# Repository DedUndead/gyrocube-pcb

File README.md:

# Gyrocube PCB design

Project is ongoing.

## Concept description 

GyroCube is a Smart-Home accessory. The GyroCube is a multipurpose cube that can perform different functions based on the cube placing. The functionality is changed by simply flipping the cube on the table. The functionalities are humidity measurements, OMA notifications, and weather-forecasts. GyroCube uses vibration modules and LEDs as the output method to notify the user of changes.<br><br>
GyroCube consists of the main station and cubes that will be in constant M2M communication. The main station handles the sensor measurements and internet communications, while the cubes react to changes in the main station. Thus, allowing the GyroCube environment to be scalable, as the user can connect as many cubes as he wants. 
The goal is to provide the user with a delightful-looking home accessory, which will also allow them to obtain helpful information in a simple, minimalistic way. 

## Topology example - Star

The HUB acts as Zigbee coordinator/router, while the cubes are end devices of the topology. HUB communicates with Wireless Access Point.

## PCB design description

PCB design for the gyrocube IoT project. Consists of several parts: x6 RGB LED PCBs, cube's MCU and main hub's MCU.
External components were used when designing the schematics

<b>Hub PCB</b>:<br>
[Microcontroller](https://app.ultralibrarian.com/details/23afb9f1-10a0-11e9-ab3a-0a3560a4cccc/Microchip/PIC32MX575F512H-80I-PT?open=backlink)<br>
[RF Tranciever (Zigbee)](https://app.ultralibrarian.com/details/42fe3879-10a0-11e9-ab3a-0a3560a4cccc/Microchip/AT86RF231-ZU?uid=8d6b40c328af52ac)<br>
[Wi-Fi Module](https://app.ultralibrarian.com/details/2b6afdaf-b24e-11ea-b5d0-0aebb021a1ea/Silicon-Labs/WFM200S022XNA2?uid=52bf9d8b68458d78)

<b>Cube MCU</b>:<br>
[Microcontroller](https://app.ultralibrarian.com/details/4b4afbe8-2e28-11eb-9033-0a34d6323d74/Microchip/PIC18F47K40-I-P?uid=9581580b9c884a46&exports=KiCAD&open=exports)<br>
[Gyroscope](https://app.ultralibrarian.com/details/68dbfc0c-1e52-11eb-9033-0a34d6323d74/STMicroelectronics/L3GD20H?uid=c097080110371f50)<br>
Humidity/Temperature sensor is custom. The library is cached in the respective folder.<br>
[Vibration coin](https://www.snapeda.com/parts/C0720B001F/Jinlong%20Machinery%20&amp;%20Electronics,%20Inc./view-part/)

## LED PCB design:

Uses ws2812b-5050 LED and 100-1000 uF filtering capacitor. The exact value is not yet specified.

The LED PCB are connected to each other with wires. The cube's PCB contains the connector to connect the first LED, that starts the series.

## Cube PCB design:

Cube PCB contains the MCU and all the peripherals.

### Cube MCU: PIC18F47K40-I/P

The MCU consists of several connection "zones": 

* SPI communication with 2 chip select slave pins 
* MCLR/PDG/PGC + Connector for PICKit programmability
* Decoupling 0.1uF capacitors
* Peripheral control pins (PWM, sleep/wake up/reset signals)

### Gyroscope and Temp/Hum sensor

MEMS Motion sensor: L3GD20H, three-axis gyroscope, utilizes SPI interface<br>
Humidity/Temperature  sensor: Si7007-A20, digital output via PWM

### Vibration motor

Diode and capacitor protect the components from voltage spikes, generated by the motor.<br>
Motor requires 75 mA, N-Channel MOSFET amplifies the current from MCU's GPIO.<br>
Intensity of vibration is handeled by PWM.

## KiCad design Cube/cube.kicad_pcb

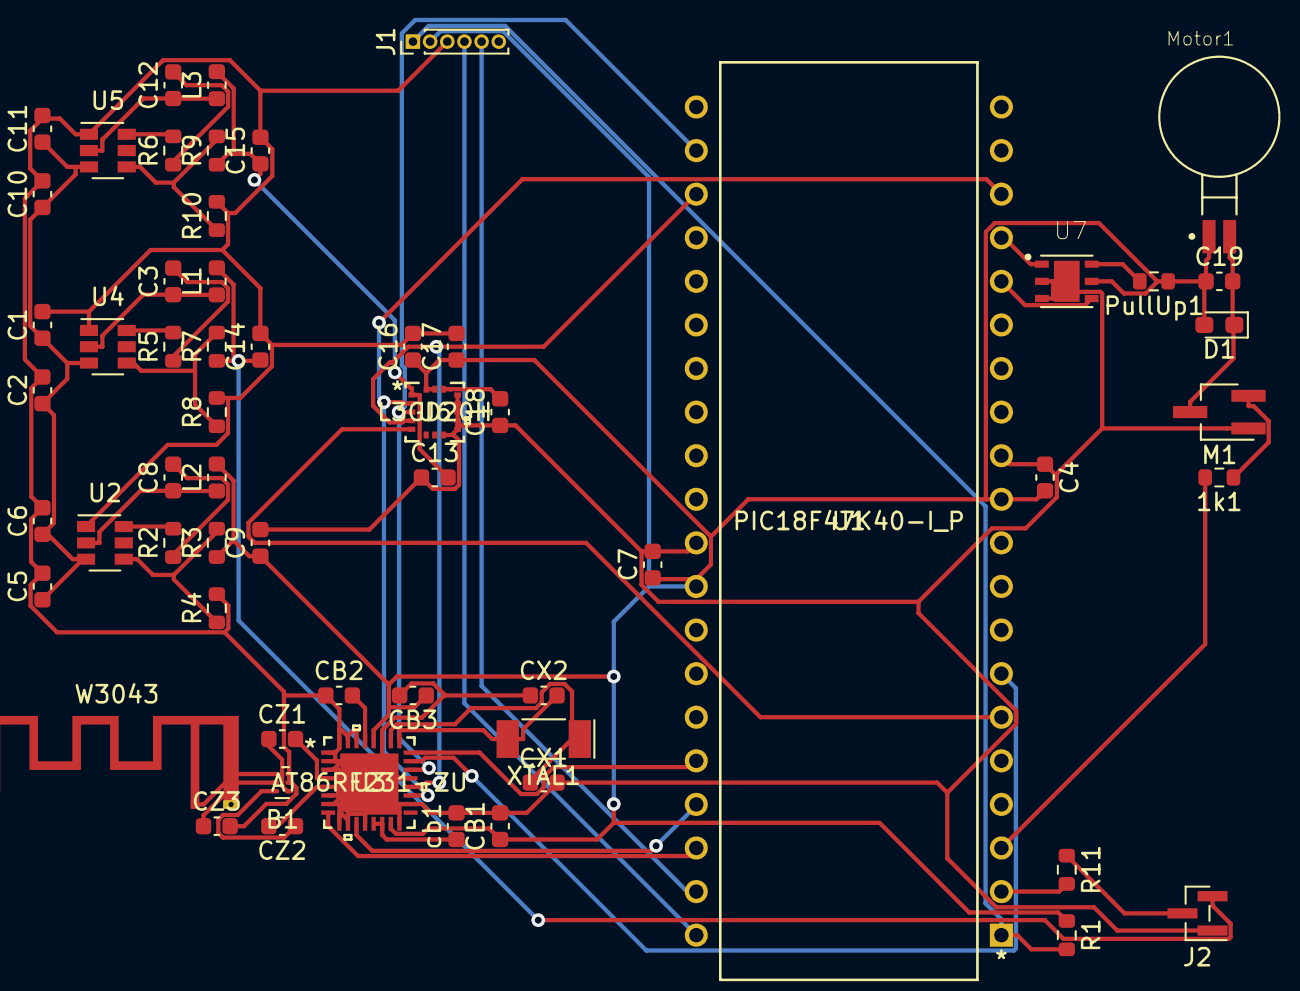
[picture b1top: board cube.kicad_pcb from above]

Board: 2 copper layers, 59 parts (0 on the bottom side), 47 nets.

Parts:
1k1: R; R_0603_1608Metric
B1: 2450FB15L0001E; Balun_Johanson_1.6x0.8mm
C1, C5, C10, C16, C18: 10uF; C_0603_1608Metric
C2, C3, C6, C8, C11, C12, C13, C17: 100nF; C_0603_1608Metric
C4, C7, C19: 0.1uF; C_0603_1608Metric
C9, C14, C15: 22uF; C_0603_1608Metric
CB1, CB2, CB3: 1uF; C_0603_1608Metric
CX1, CX2: 12pF; C_0603_1608Metric
CZ1, CZ2, CZ3: 22pF; C_0603_1608Metric
D1: DIODE; D_0603_1608Metric_Pad1.05x0.95mm_HandSolder
J1: Conn_01x06_Male; PinHeader_1x06_P1.00mm_Vertical
J2: Conn_01x03_Male; PinHeader_1x03_P1.00mm_Vertical_SMD_Pin1Left
L1: 5.6uH; L_0603_1608Metric
L2: 4.7uH; L_0603_1608Metric
L3: 2.2uH; L_0603_1608Metric
M1: MNMOS; SOT-23W_Handsoldering
Motor1: C0720B001F; XDCR_C0720B001F
PullUp1: 10k; R_0603_1608Metric
R1: 1k; R_0603_1608Metric
R2, R5, R6: 30; R_0603_1608Metric
R3: 30.9k; R_0603_1608Metric
R4, R8, R10: 10k; R_0603_1608Metric
R7: 52.3k; R_0603_1608Metric
R9: 12.4k; R_0603_1608Metric
R11: 330; R_0603_1608Metric
U1: PIC18F47K40-I_P; PIC18F47K40-I&slash_P
U2, U4, U5: TPS56339DDC; SOT-23-6
U3: AT86RF231-ZU
U6: L3GD20H
U7: Si7007-A20; SON100P300X300X80-7N
W3043: 2.4GHz; Texas_SWRA117D_2.4GHz_Left
XTAL1: CX-4025 16Mhz; Crystal_SMD_MicroCrystal_CC4V-T1A-2Pin_5.0x1.9mm
cb1: 1uF; C_0603_1608Metric

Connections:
+1V8: C13.2, C15.1, L3.2, R9.1, U6.1
+3V3: C4.2, C7.1, C9.1, C16.1, C17.1, C19.1, CB1.1, CB3.1, D1.2, J1.2, L2.2, Motor1.1, PullUp1.1, R1.1, R3.1, U1.11, U1.32, U3.15, U3.28, U6.15, U6.16, U7.5
+5V: C14.1, J2.3, L1.2, R7.1
GND: B1.5, B1.6, C1.2, C2.2, C4.1, C5.2, C6.2, C7.2, C9.2, C10.2, C11.2, C13.1, C14.2, C15.2, C16.2, C17.2, C18.1, CB1.2, CB2.1, CB3.2, CX1.2, CX2.1, CZ3.2, J1.3, J2.1, M1.1, R4.2, R8.2, R10.2, U1.12, U1.31, U2.1, U3.1, U3.2, U3.3, U3.6, U3.7, U3.9, U3.10, U3.12, U3.16, U3.18, U3.21, U3.27, U3.30, U3.31, U3.32, U3.33, U4.1, U5.1, U6.8, U6.9, U6.10, U6.11, U6.12, U6.13, U7.2, U7.3, U7.7, cb1.2
IRQ_ZGB: U1.36, U3.24
LED_DATA: R11.2, U1.2
MCLR: J1.1, R1.2, U1.1
MOTOR_OUT: 1k1.2, U1.3
unnamed: 1k1.1, M1.2
unnamed: B1.1, W3043.1
unnamed: B1.2, CZ3.1
unnamed: B1.3, CZ2.1
unnamed: B1.4, CZ1.1
unnamed: C3.1, L1.1, U4.2
unnamed: C3.2, R5.1
unnamed: C8.1, L2.1, U2.2
unnamed: C8.2, R2.1
unnamed: C12.1, L3.1, U5.2
unnamed: C12.2, R6.1
unnamed: C18.2, U6.14
unnamed: C19.2, D1.1, M1.3, Motor1.2
unnamed: CB2.2, U3.29
unnamed: CX1.1, U3.26, XTAL1.1
unnamed: CX2.2, U3.25, XTAL1.2
unnamed: CZ1.2, U3.4
unnamed: CZ2.2, U3.5
unnamed: J2.2, R11.1
unnamed: PullUp1.2, U7.6
unnamed: R2.2, U2.6
unnamed: R3.2, R4.1, U2.4
unnamed: R5.2, U4.6
unnamed: R6.2, U5.6
unnamed: R7.2, R8.1, U4.4
unnamed: R9.2, R10.1, U5.4
unnamed: U3.13, U3.14, cb1.1
PGC: J1.5, U1.39
PGD: J1.4, U1.40
RESET_ZGB: U1.38, U3.8
RH_OUT: U1.16, U7.4
SLP_TR: U1.37, U3.11
SPI_CLK: U1.18, U3.19, U6.2
SPI_CS1: U1.7, U3.23
SPI_CS2: U1.6, U6.5
SPI_MISO: U1.23, U3.20, U6.4
SPI_MOSI: U1.22, U3.22, U6.3
TEMP_OUT: U1.17, U7.1
VCC: C1.1, C2.1, C5.1, C6.1, C10.1, C11.1, U2.3, U4.3, U5.3

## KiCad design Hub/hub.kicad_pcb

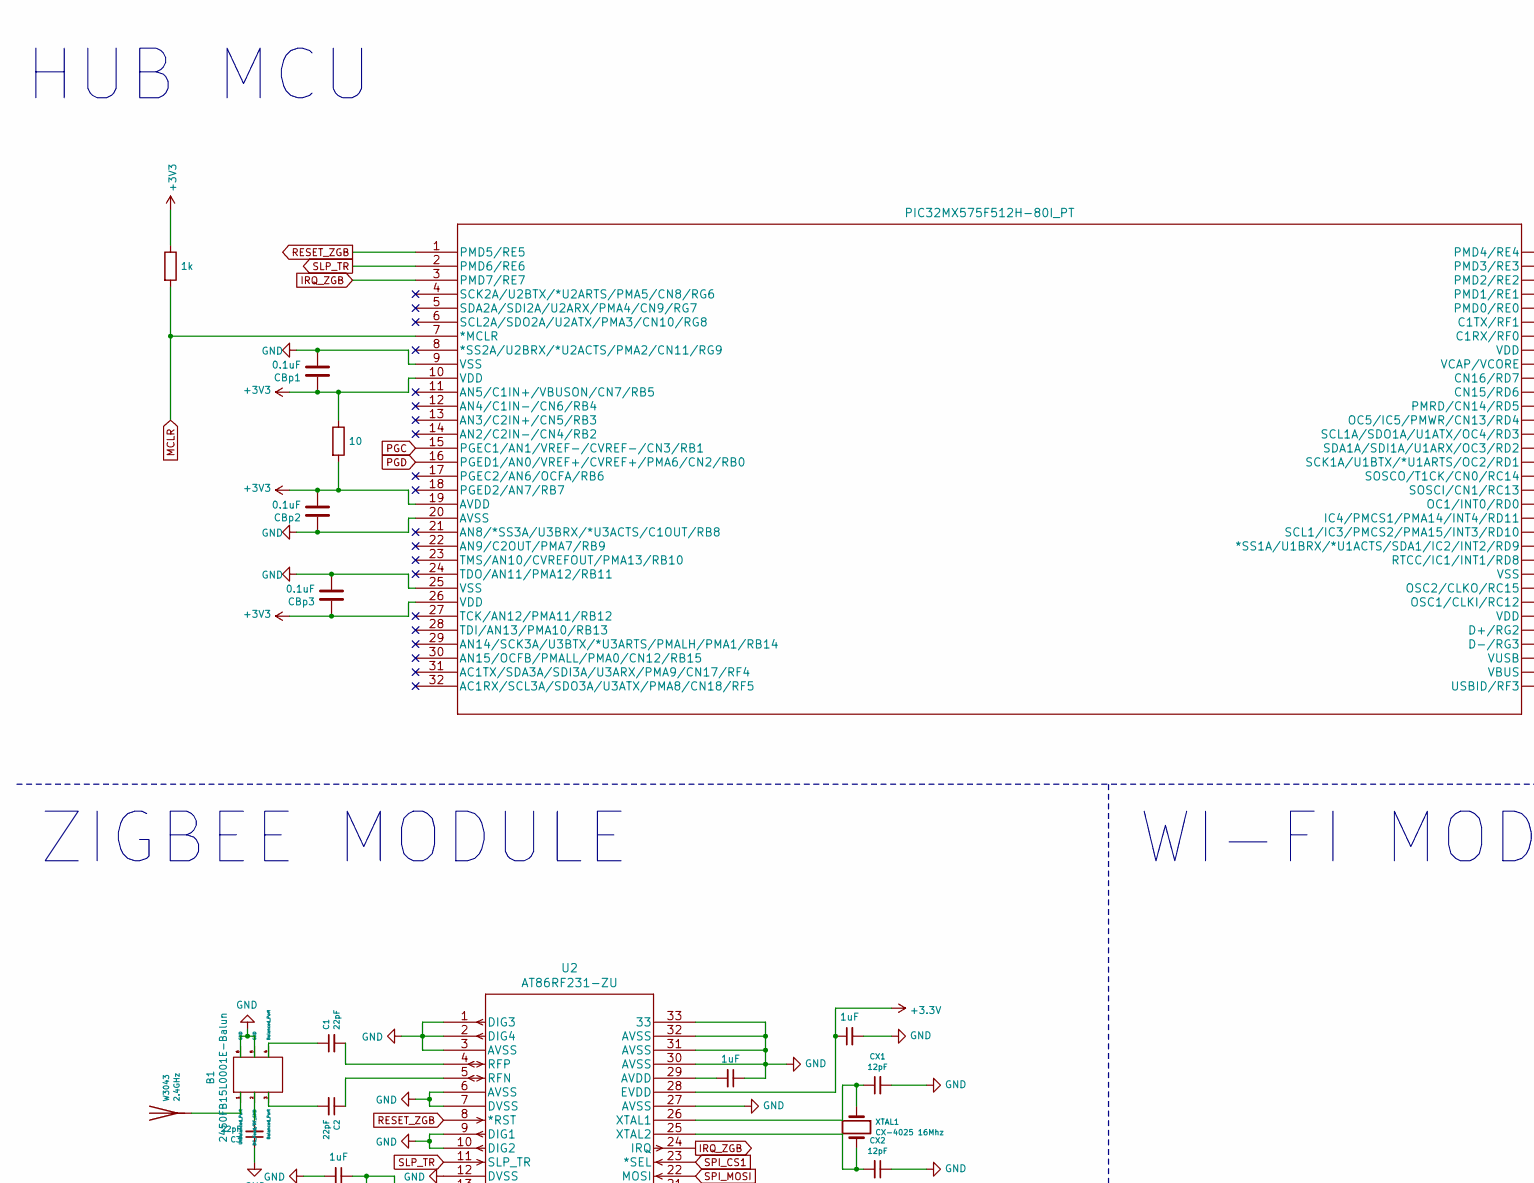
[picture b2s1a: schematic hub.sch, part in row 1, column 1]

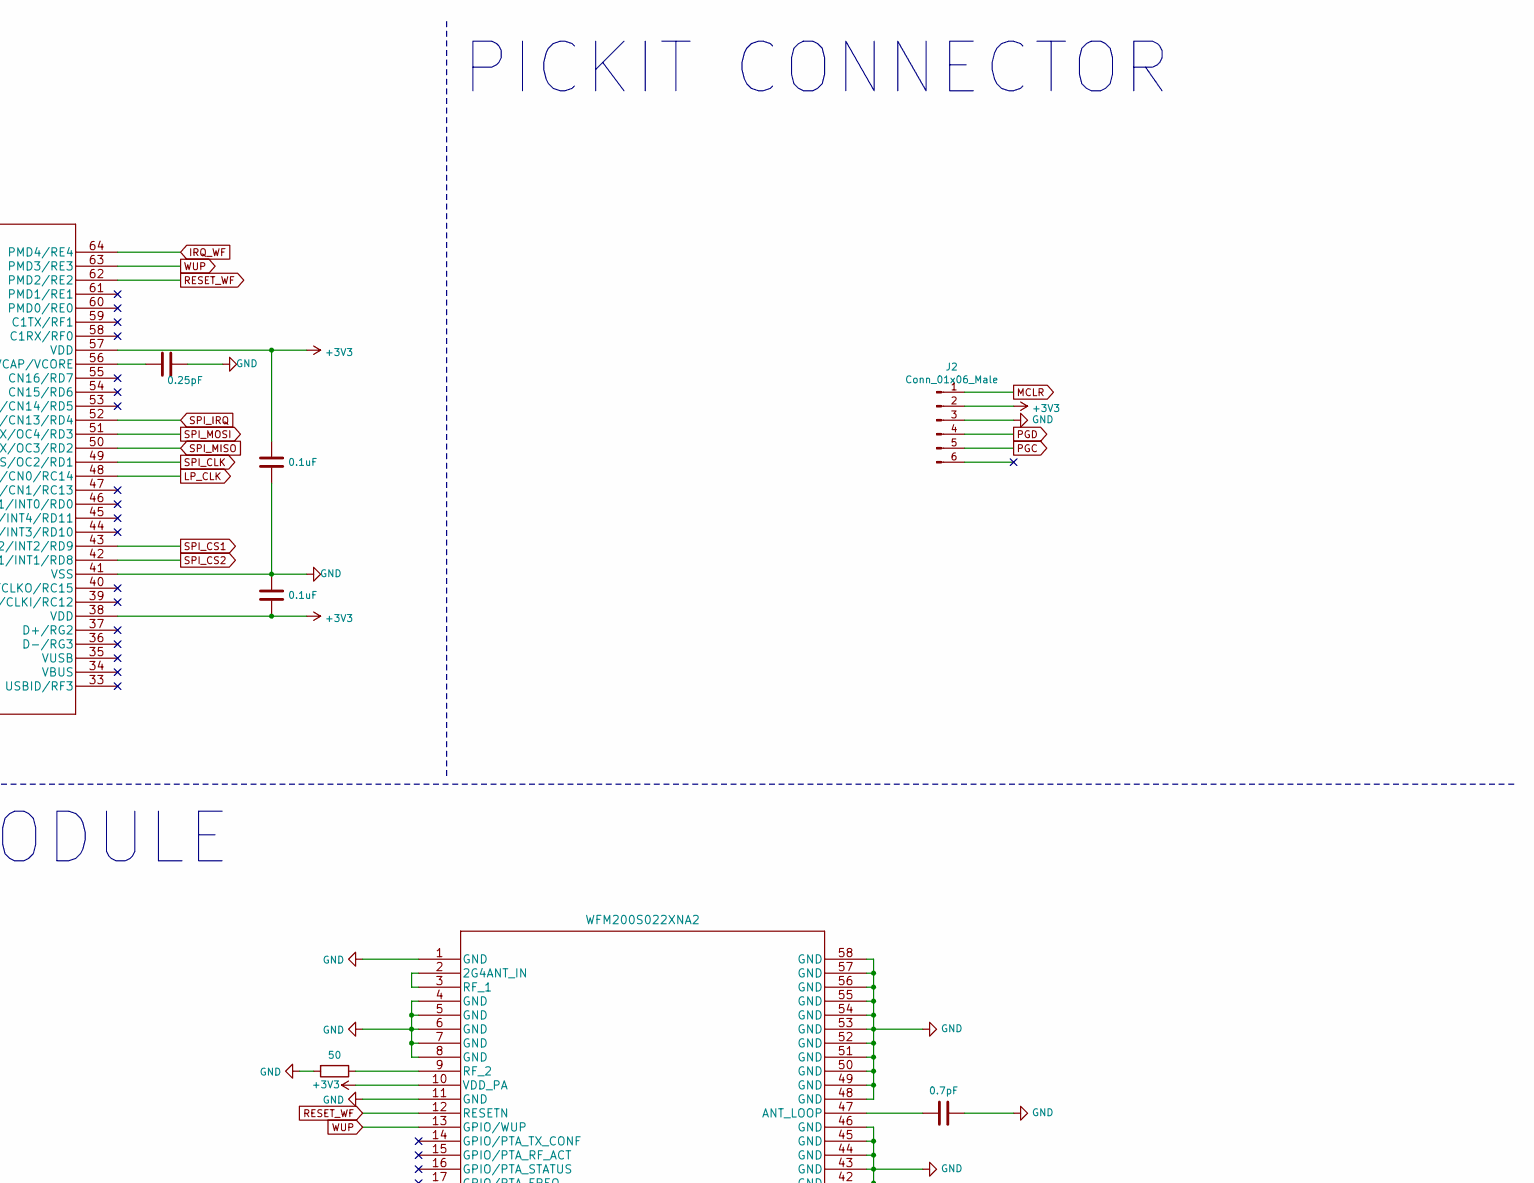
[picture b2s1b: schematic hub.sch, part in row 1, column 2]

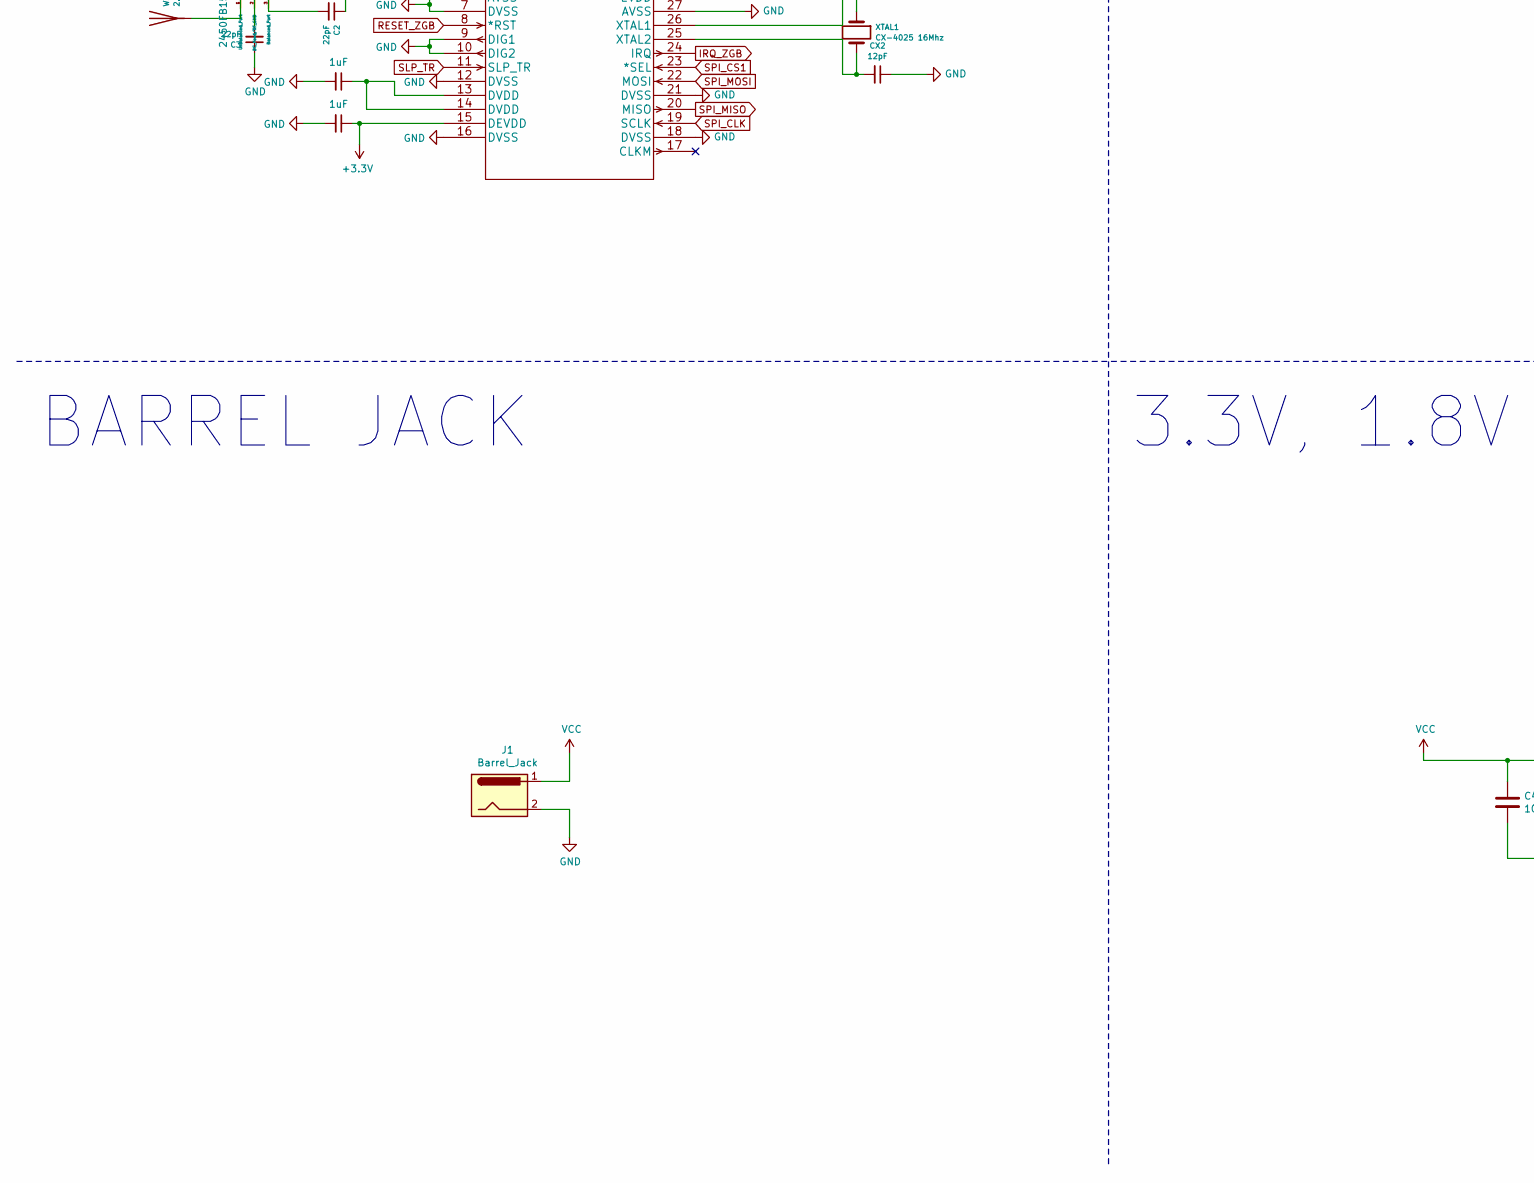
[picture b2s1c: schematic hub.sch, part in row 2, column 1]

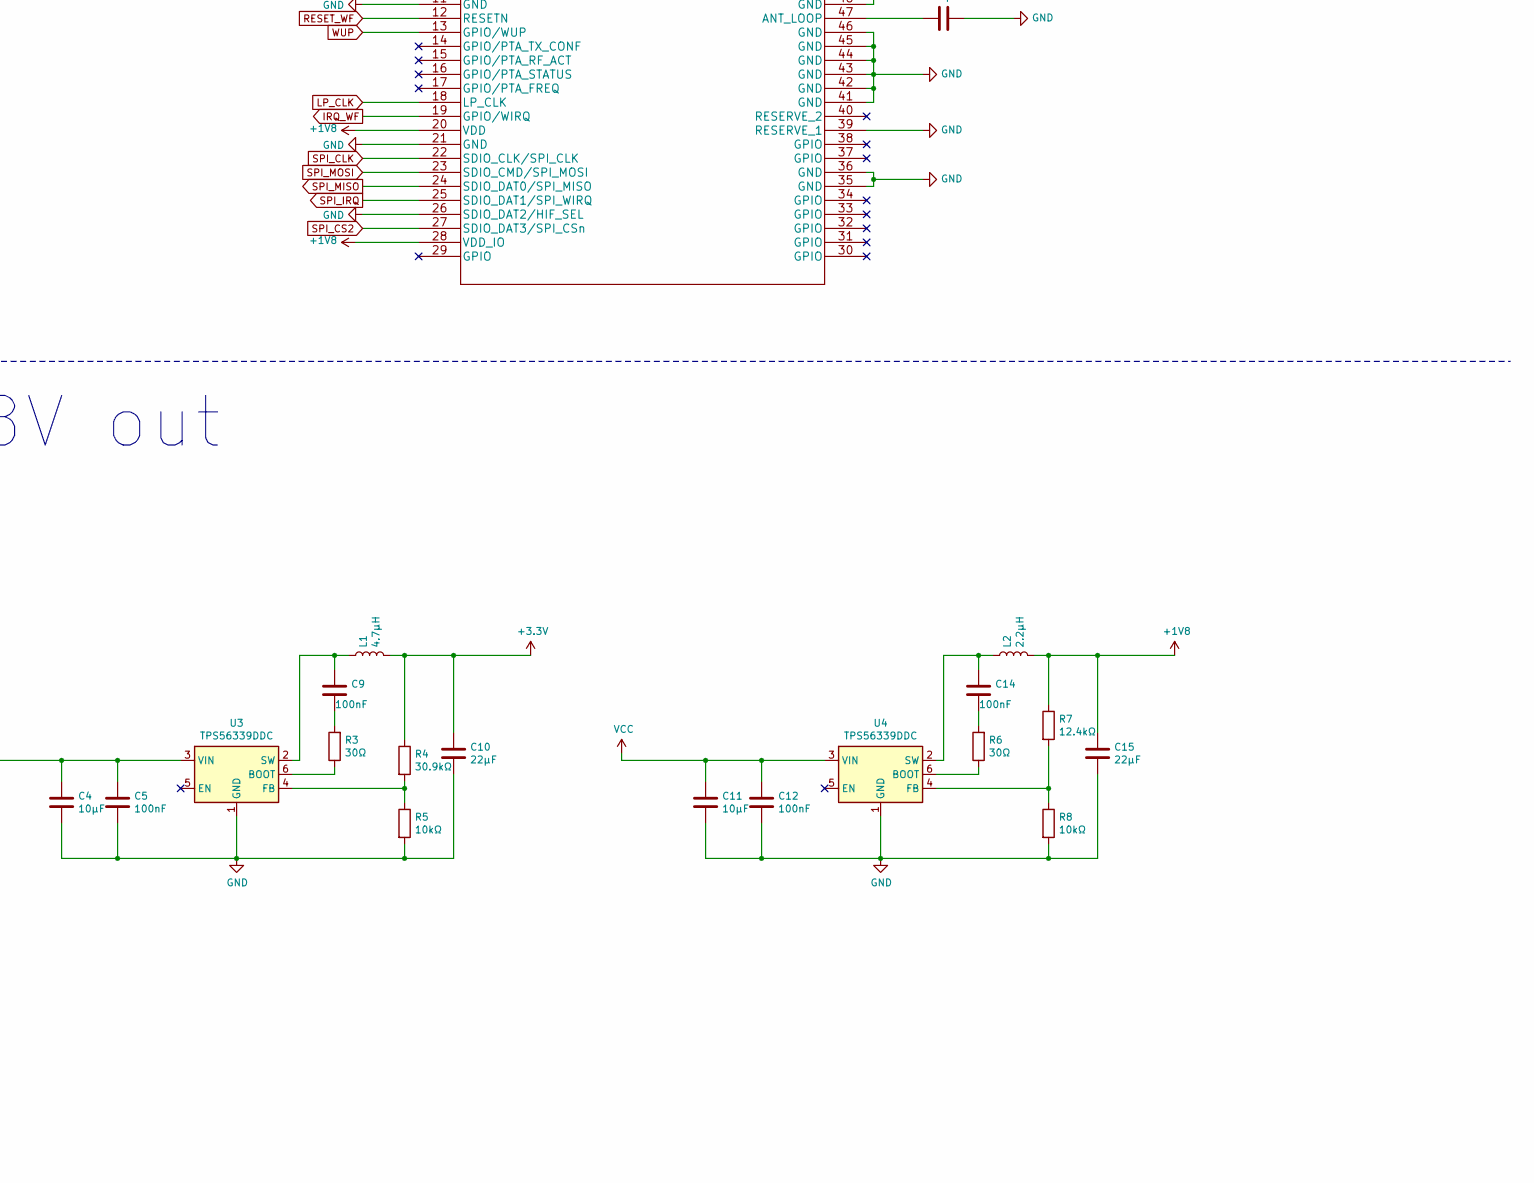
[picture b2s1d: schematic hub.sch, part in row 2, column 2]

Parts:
B1: 2450FB15L0001E-Balun; Balun_Johanson_1.6x0.8mm
C1, C2, C3: 22pF; C_0603_1608Metric
C4, C11: 10µF; C_0603_1608Metric
C5, C9, C12, C14: 100nF; C_0603_1608Metric
C6: 0.25pF; C_0603_1608Metric
C7, C8: 0.1uF; C_0603_1608Metric
C10, C15: 22µF; C_0603_1608Metric
C13: 0.7pF; C_0603_1608Metric
CB1, CB2, CB3: 1uF; C_0603_1608Metric
CBp1, CBp2, CBp3: 0.1uF; C_0603_1608Metric
CX1, CX2: 12pF; C_0603_1608Metric
J1: Barrel_Jack; BarrelJack_CUI_PJ-063AH_Horizontal
J2: Conn_01x06_Male; PinHeader_1x06_P1.00mm_Vertical
L1: 4.7µH; L_0603_1608Metric
L2: 2.2µH; L_0603_1608Metric
R1: 1k; R_0603_1608Metric
R2: 50; R_0603_1608Metric
R3, R6: 30Ω; R_0603_1608Metric
R4: 30.9kΩ; R_0603_1608Metric
R5, R8: 10kΩ; R_0603_1608Metric
R7: 12.4kΩ; R_0603_1608Metric
RR1: 10; R_0603_1608Metric
U1: PIC32MX575F512H-80I_PT; PIC32MX575F512H-80I&slash_PT
U2: AT86RF231-ZU
U3, U4: TPS56339DDC; SOT-23-6
W3043: 2.4GHz; Texas_SWRA117D_2.4GHz_Left
WiFi1: WFM200S022XNA2
XTAL1: CX-4025 16Mhz; Crystal_SMD_MicroCrystal_CC4V-T1A-2Pin_5.0x1.9mm
cb1: 1uF; C_0603_1608Metric

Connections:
+1V8: C15.1, L2.2, R7.1, WiFi1.20 (VDD), WiFi1.28 (VDD_IO)
GND: B1.5 (GND), B1.6 (GND), C3.1, C4.2, C5.2, C6.1, C7.2, C8.1, C10.2, C11.2, C12.2, C13.1, C15.2, CB1.2, CB2.1, CB3.2, CBp1.2, CBp2.1, CBp3.2, CX1.2, CX2.1, J1.2, J2.3, R2.2, R5.2, R8.2, U1.9 (VSS), U1.20 (AVSS), U1.25 (VSS), U1.41 (VSS), U2.1 (DIG3), U2.2 (DIG4), U2.3 (AVSS), U2.6 (AVSS), U2.7 (DVSS), U2.9 (DIG1), U2.10 (DIG2), U2.12 (DVSS), U2.16 (DVSS), U2.18 (DVSS), U2.21 (DVSS), U2.27 (AVSS), U2.30 (AVSS), U2.31 (AVSS), U2.32 (AVSS), U2.33, U3.1 (GND), U4.1 (GND), WiFi1.1 (GND), WiFi1.4 (GND), WiFi1.5 (GND), WiFi1.6 (GND), WiFi1.7 (GND), WiFi1.8 (GND), WiFi1.11 (GND), WiFi1.21 (GND), WiFi1.26 (SDIO_DAT2/HIF_SEL), WiFi1.35 (GND), WiFi1.36 (GND), WiFi1.39 (RESERVE_1), WiFi1.41 (GND), WiFi1.42 (GND), WiFi1.43 (GND), WiFi1.44 (GND), WiFi1.45 (GND), WiFi1.46 (GND), WiFi1.48 (GND), WiFi1.49 (GND), WiFi1.50 (GND), WiFi1.51 (GND), WiFi1.52 (GND), WiFi1.53 (GND), WiFi1.54 (GND), WiFi1.55 (GND), WiFi1.56 (GND), WiFi1.57 (GND), WiFi1.58 (GND), cb1.2
IRQ_WF: U1.64 (PMD4/RE4), WiFi1.19 (GPIO/WIRQ)
IRQ_ZGB: U1.3 (PMD7/RE7), U2.24 (IRQ)
LP_CLK: U1.48 (SOSCO/T1CK/CN0/RC14), WiFi1.18 (LP_CLK)
MCLR: J2.1, R1.2, U1.7 (*MCLR)
unnamed: B1.1 (Unbalanced_Port), W3043.1
unnamed: B1.2 (DC_Feed/RF_GND), C3.2
unnamed: B1.3 (Balanced_Port), C2.2
unnamed: B1.4 (Balanced_Port), C1.1
unnamed: C1.2, U2.4 (RFP)
unnamed: C2.1, U2.5 (RFN)
unnamed: C6.2, U1.56 (VCAP/VCORE)
unnamed: C9.1, L1.1, U3.2 (SW)
unnamed: C9.2, R3.2
unnamed: C13.2, WiFi1.47 (ANT_LOOP)
unnamed: C14.1, L2.1, U4.2 (SW)
unnamed: C14.2, R6.2
unnamed: CB2.2, U2.29 (AVDD)
unnamed: CX1.1, U2.26 (XTAL1), XTAL1.1
unnamed: CX2.2, U2.25 (XTAL2), XTAL1.2
unnamed: R2.1, WiFi1.9 (RF_2)
unnamed: R3.1, U3.6 (BOOT)
unnamed: R4.2, R5.1, U3.4 (FB)
unnamed: R6.1, U4.6 (BOOT)
unnamed: R7.2, R8.1, U4.4 (FB)
unnamed: U2.13 (DVDD), U2.14 (DVDD), cb1.1
unnamed: WiFi1.2 (2G4ANT_IN), WiFi1.3 (RF_1)
PGC: J2.5, U1.15 (PGEC1/AN1/VREF-/CVREF-/CN3/RB1)
PGD: J2.4, U1.16 (PGED1/AN0/VREF+/CVREF+/PMA6/CN2/RB0)
RESET_WF: U1.62 (PMD2/RE2), WiFi1.12 (RESETN)
RESET_ZGB: U1.1 (PMD5/RE5), U2.8 (*RST)
SLP_TR: U1.2 (PMD6/RE6), U2.11 (SLP_TR)
SPI_CLK: U1.49 (SCK1A/U1BTX/*U1ARTS/OC2/RD1), U2.19 (SCLK), WiFi1.22 (SDIO_CLK/SPI_CLK)
SPI_CS1: U1.43 (*SS1A/U1BRX/*U1ACTS/SDA1/IC2/INT2/RD9), U2.23 (*SEL)
SPI_CS2: U1.42 (RTCC/IC1/INT1/RD8), WiFi1.27 (SDIO_DAT3/SPI_CSn)
SPI_IRQ: U1.52 (OC5/IC5/PMWR/CN13/RD4), WiFi1.25 (SDIO_DAT1/SPI_WIRQ)
SPI_MISO: U1.50 (SDA1A/SDI1A/U1ARX/OC3/RD2), U2.20 (MISO), WiFi1.24 (SDIO_DAT0/SPI_MISO)
SPI_MOSI: U1.51 (SCL1A/SDO1A/U1ATX/OC4/RD3), U2.22 (MOSI), WiFi1.23 (SDIO_CMD/SPI_MOSI)
VCC: C4.1, C5.1, C11.1, C12.1, J1.1, U3.3 (VIN), U4.3 (VIN)
WUP: U1.63 (PMD3/RE3), WiFi1.13 (GPIO/WUP)

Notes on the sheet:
ZIGBEE MODULE
HUB MCU
WI-FI MODULE
BARREL JACK
3.3V, 1.8V out
PICKIT CONNECTOR

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
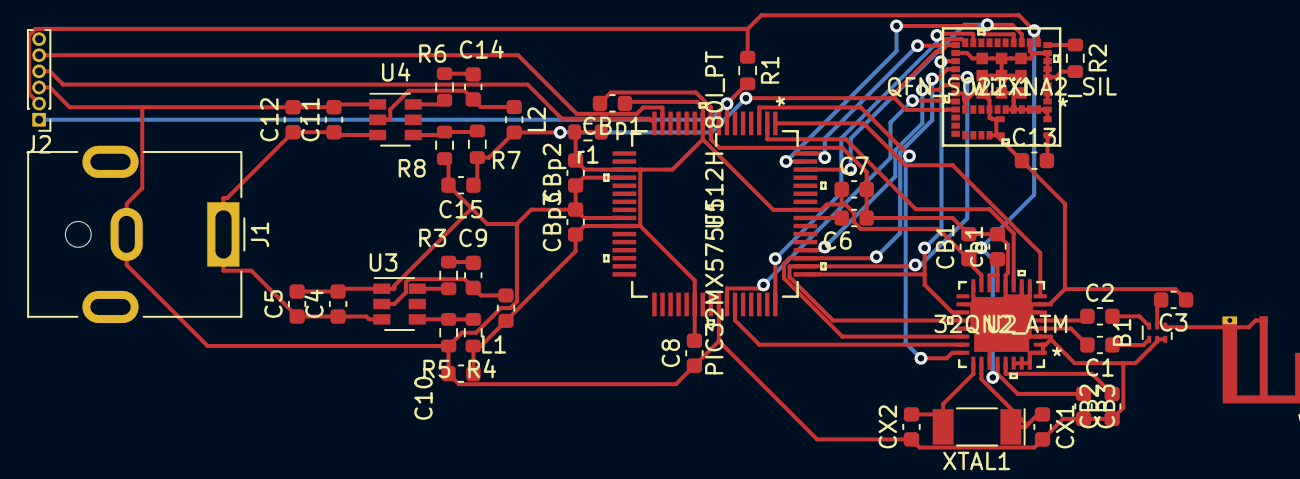
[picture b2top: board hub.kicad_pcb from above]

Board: 2 copper layers, 45 parts (0 on the bottom side), 42 nets.

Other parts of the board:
r1: 10; R_0603_1608Metric

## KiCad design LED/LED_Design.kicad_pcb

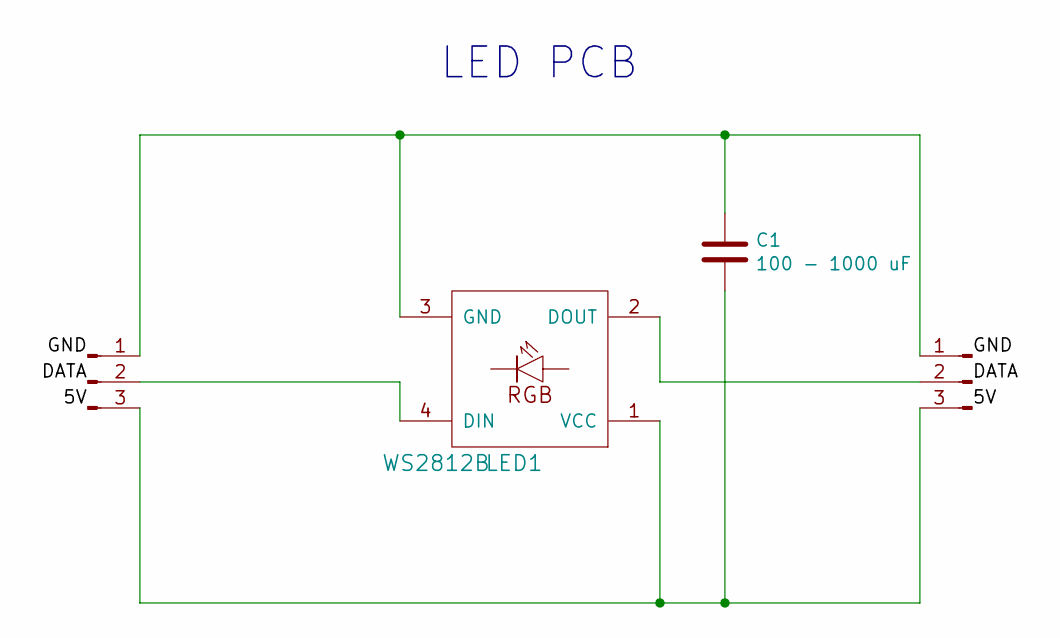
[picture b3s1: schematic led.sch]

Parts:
C1: 100 - 1000 uF; C_0603_1608Metric
J1, J2: Conn_01x03_Male; SolderWire-0.1sqmm_1x03_P3.6mm_D0.4mm_OD1mm
LED1: WS2812B; LED_WS2812B_PLCC4_5.0x5.0mm_P3.2mm

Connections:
unnamed: C1.1, J1.1, J2.1, LED1.3 (GND)
unnamed: C1.2, J1.3, J2.3, LED1.1 (VCC)
unnamed: J1.2, LED1.4 (DIN)
unnamed: J2.2, LED1.2 (DOUT)

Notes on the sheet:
LED PCB

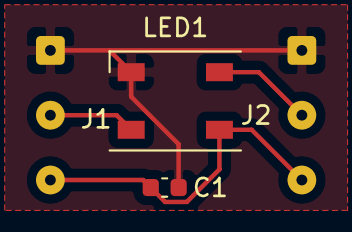
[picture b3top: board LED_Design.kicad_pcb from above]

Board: 2 copper layers, 4 parts (0 on the bottom side), 4 nets.

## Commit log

2021-04-13 Add separate sheet for each contributor
2021-04-16 Add LED PCB design
2021-04-17 Create image folder for readme
2021-04-17 Add images for readme
2021-04-18 changed led capacitor value
2021-04-18 updated led schematic
2021-04-18 Add HUB PCB schema
2021-04-19 Edit HUB PCB
2021-04-19 Finish hub pcb schema
2021-04-19 Add cube PCB design
2021-04-19 Return libraries
2021-04-19 project structure change
2021-04-19 Added humidity/gyro sensors to the cube pcb
2021-04-19 Edit cube pcb style
2021-04-20 Finish LED scematics
2021-04-20 Add minor changes
2021-04-20 Update
    Zigbee update:
    - Added custom made symbol: SMD Balun - 2450FB15L0001E
    - Added Antenna - Ceramic chip: W3043
    Note: There might be a missing capacitor in the communication between the antenna to the Balun - some circuit reference does have it some doesn't
2021-04-20 Add motor to the cube schematics
2021-04-20 added power
2021-04-20 fixed power circuit
2021-04-20 Add power supply changes
2021-04-20 added both voltages to the hub
2021-04-20 Add programmable connectors
2021-04-21 Fix minor mistakes after the presentation
2021-04-25 hub pcb stuck
2021-04-26 hub pcb routed
2021-04-26 Add components to cube
2021-04-27 Add cube pcb layout
2021-04-27 added cube routes
2021-09-27 Create LICENSE

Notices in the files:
parts and their libraries:
Copyright 2016 Accelerated Designs. All rights reserved.
